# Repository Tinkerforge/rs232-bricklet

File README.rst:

RS232 Bricklet
==============

This repository contains the firmware source code and the hardware design
files. The documentation generator configs can be found at
https://github.com/Tinkerforge/generators

Repository Content
------------------

software/:
 * examples/: Examples for all supported languages
 * build/: Compiled files
 * src/: Source code of firmware
 * Makefile: Makefile to build project

hardware/:
 * Contains KiCad project files and additionally schematics as PDF

datasheets/:
 * Contains datasheets for sensors and complex ICs that are used

Hardware
--------

The hardware is designed with the open source EDA Suite KiCad
(http://www.kicad.org). Before you are able to open the files,
you have to install the Tinkerforge kicad-libraries
(https://github.com/Tinkerforge/kicad-libraries). You can either clone
them directly in hardware/ or clone them in a separate folder and
symlink them into hardware/
(ln -s kicad_path/kicad-libraries project_path/hardware). After that you
can open the .pro file in hardware/ with KiCad and from there view and
modify the schematics and the PCB layout.

Software
--------

If you want to do your own Brick/Bricklet firmware development we highly
recommend that you use our build environment setup script and read the
tutorial (https://www.tinkerforge.com/en/doc/Tutorials/Tutorial_Build_Environment/Tutorial.html).

To compile the C code we recommend you to install the newest GNU Arm Embedded
Toolchain (https://launchpad.net/gcc-arm-embedded/+download).
You also need to install bricklib (https://github.com/Tinkerforge/bricklib)
and brickletlib (https://github.com/Tinkerforge/brickletlib).

You can either clone it directly in software/src/ or clone it in a
separate folder and symlink it into software/src/
(ln -s bricklib_path/bricklib project_path/software/src/ and
ln -s brickletlib_path/brickletlib project_path/software/src/).
Finally make sure to have CMake installed
(http://www.cmake.org/cmake/resources/software.html).

After that you can build the firmware by invoking make in software/.
The firmware (.bin) can then be found in software/build/ and uploaded
with brickv (click button "Flashing" on start screen).

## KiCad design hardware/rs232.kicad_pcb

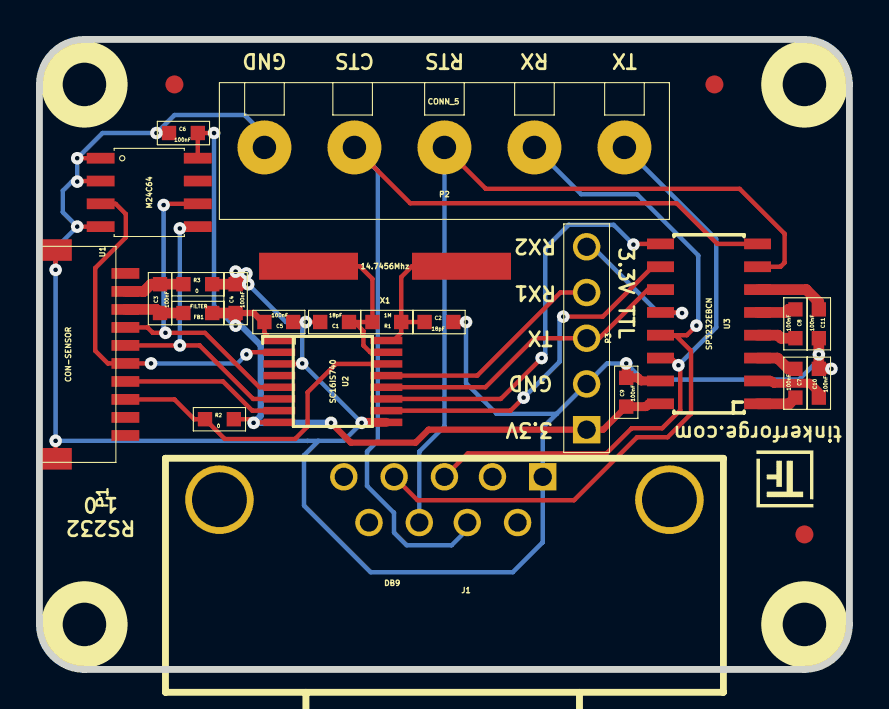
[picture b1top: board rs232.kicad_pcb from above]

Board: 2 copper layers, 45.0 x 35.0 mm, 32 parts (0 on the bottom side), 26 nets.

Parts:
C1, C2: 18pF; 0603
C3, C4, C5, C6, C7, C8, C9, C10, C11: 100nF; 0603
FB1: FILTER; 0603
Fiducial_Mark: VAL**; Fiducial_Mark
Fiducial_Mark#2, Fiducial_Mark#3: VAL**; Fiducial_Mark
J1: DB9; SUB09-EU
P1: CON-SENSOR
P2: CONN_5; AKL_5_5
P3: CONN_5; pin_array_5x1
R1: 1M; 0603
R2, R3: 0; 0603
U1: M24C64; SOIC8
U2: SC16IS740; TSSOP16
U3: SP3232EBCN; SOIC16
U4, U5, U6, U7: DRILL; DRILL_NP
VAL: WEEE_7mm
VAL#2: CE_5mm
X1: 14.7456Mhz; HC49_US

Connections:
GND: C1.1, C2.1, C4.1, C5.2, C6.2, C9.1, C10.1, C11.1, J1.1, P1.EP, P2.1, P3.2, R3.1, U1.1, U1.2, U1.4, U2.3, U2.9, U3.15
unnamed: C1.2, R1.1, U2.15, X1.2
unnamed: C2.2, R1.2, U2.16, X1.1
unnamed: C3.1, P1.2, R3.2
unnamed: C3.2, FB1.1, P1.3
unnamed: C7.1, U3.1
unnamed: C7.2, U3.3
unnamed: C8.1, U3.4
unnamed: C8.2, U3.5
unnamed: C10.2, U3.2
unnamed: C11.2, U3.6
unnamed: J1.3, P2.5, U3.14
unnamed: J1.4, P2.4, U3.13
unnamed: J1.7, P2.2, U3.8
unnamed: J1.8, P2.3, U3.7
unnamed: P1.6, U1.3, U2.2
unnamed: P1.7, U2.7
unnamed: P1.8, R2.2, U2.14
unnamed: P3.3, U2.12, U3.11
unnamed: P3.4, U2.13
unnamed: P3.5, U3.12
unnamed: U2.10, U3.10
unnamed: U2.11, U3.9
SCL: P1.4, U1.6, U2.5
SDA: P1.5, U1.5, U2.6
VCC: C4.2, C5.1, C6.1, C9.2, FB1.2, P3.1, R2.1, U1.8, U2.1, U2.8, U3.16

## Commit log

2015-03-05 Add first stub implementation of API
2015-03-25 Implement RS232 API
2015-03-26 add hardware files for rs232 bricklet
2015-03-26 add schematic
2015-04-02 run drc
2015-04-16 Add .gitignore
2015-04-24 drc executed
2015-04-30 Make sure setter return message if necessary
2015-04-30 Add Python examples
2015-05-07 Add C example
2015-05-07 Add comment
2015-05-07 Add VB.NET example
2015-05-07 Add C# example
2015-05-07 Add Python example
2015-05-07 Add Delphi examples
2015-05-07 Add Java example
2015-05-07 Add JavaScript examples
2015-05-07 Add Perl example
2015-05-07 Add PHP example
2015-05-07 Use '\0' for empty string
2015-05-07 Add Ruby example
2015-05-07 Call enable_callback before writing string
2015-05-07 Add Shell example
2015-05-10 Add retrun value to write function (written chars)
2015-06-17 Rename enable_callback to enable_read_callback in examples
2015-06-17 Rename enable_callback to enable_read_callback in plugin
2015-06-19 Remove Python example from wrong directory
2015-06-19 Add LabVIEW and Mathematica examples
    Also clean up other examples.
2015-06-22 shell: Use array ellipsis in example
2015-06-23 perl: Fix char_array_to_string helper
2015-06-24 csharp: Add missing System namespace
2015-07-07 java: Simplify char array creation
2015-07-08 Add MATLAB loopback example
2015-07-08 Add Octave example
2015-07-25 Make JavaScript browser example textarea readonly
2015-07-27 Fix import order in Java example
2015-07-29 Reformat changelog
2015-08-07 Use full device class name in Python example
2015-08-12 Fix minor warnings in C/C++ example
2015-08-14 Fix typo
2015-08-18 Make reading of RHR register more efficient
    * This should allow longer bursts with higher bandwith
    * Also add callbacks for overrun, framing and parity errors
2015-08-18 Add Changelog entry for v2.0.1
2015-09-08 Add support for break condition
2015-09-09 Duplicate cmake call to fix bug during cmake creation
2015-11-12 matlab: Fix callback handling for R2014a
    http://undocumentedmatlab.com/blog/matlab-callbacks-for-java-events-in-r2014a
2015-11-12 Generator based example cleanup
2015-11-12 shell: Stop callback dispatch before exit
2015-11-25 Include date and commit into changelog
2016-02-24 Fix typos in examples
2016-04-07 Whitespace
2016-05-18 c: Add missing device destroy call
2016-06-29 octave: Fix wrong comment
2016-07-01 Make the change UID comment more explicit
2016-11-08 Remove unnecessary read
2016-11-08 Make sure we don't have uncessary i2c select/deselect
2016-11-08 fix source code bugs, no compiling
2016-11-08 Make sure we always call select before i2c read
2016-12-09 fix baudrate setting bug
    baudrate settings were not working for baudrates lower than 4800 baud
2017-01-03 hardware adaption: fix reset to ground
2017-01-09 Change RESET beahvior to be compatible with new hardware version
2017-01-09 Increase software version to 2.0.3
2017-01-16 Add changelog commit after the fact
2017-04-20 Adapt examples
2017-04-21 Calling read() returns zero data if read callback is enabled
2017-06-02 octave: Use javaObject instead of deprecated java_new
2017-06-06 examples: Some style cleanup
2017-06-06 examples: Unify location of description
2017-06-14 php: Explode doesn't work with an empty delimiter
2017-07-18 perl: Fix array/ref mixup
2017-07-18 vbnet: Simplify ASCII handling code
2017-11-30 Update examples from generator
2017-12-07 mathematica: Also generate .nb files
2018-02-19 javascript: Close div tag correctly
2018-02-20 Cleanup KiCad libraries config
    Ensure LibDir=kicad-libraries and LibName1=tinkerforge.
    Remove special library.
2018-05-24 perl: Use strict in examples
2018-05-24 c: Simpler variable style
2018-07-11 Add Makefile with docker support
2018-07-11 Update directory structure and build instructions
2018-07-11 Remove obsolete generate_makefile scripts
2018-07-17 delphi: Fix string/array conversion for Delphi XE
2018-11-06 Add rust examples
2018-11-07 rust: Accept host names for ip connection, fix naming inconsistencies
2018-11-07 rust: Rename callback receivers.
2018-12-14 Add go examples.
2018-12-18 go: Change import path.
2018-12-18 go: Change import path again.
2019-01-24 mqtt: Add examples.
2019-01-24 mqtt: Remove executable bit in example permissions.
2019-01-24 go: Minor example fixes.
2019-08-22 c: Adapt to bindings changes
2020-01-14 examples: Use python3 input by default.
2020-02-25 Add frame available callback and read frame function.
2020-02-28 Cache pointers to squeeze out some firmware bytes.
2020-02-28 Append to changelog.
2020-02-28 Add commit ref to changelog.
2020-02-28 Fix changelog.
2020-03-18 rust: Update to new skeleton
2021-10-25 Update KiCad link
    https://www.kicad.org/blog/2021/10/Avoid-links-to-former-kicad-domain/
2022-07-06 Add license files.

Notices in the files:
hardware/rs232.kicad_pcb:
Licensed under CERN OHL v.1.1
Copyright (©) 2015, B.Nordmeyer
Copyright Tinkerforge GmbH 2015.
This documentation describes Open Hardware and is licensed under the
CERN OHL v. 1.1.
